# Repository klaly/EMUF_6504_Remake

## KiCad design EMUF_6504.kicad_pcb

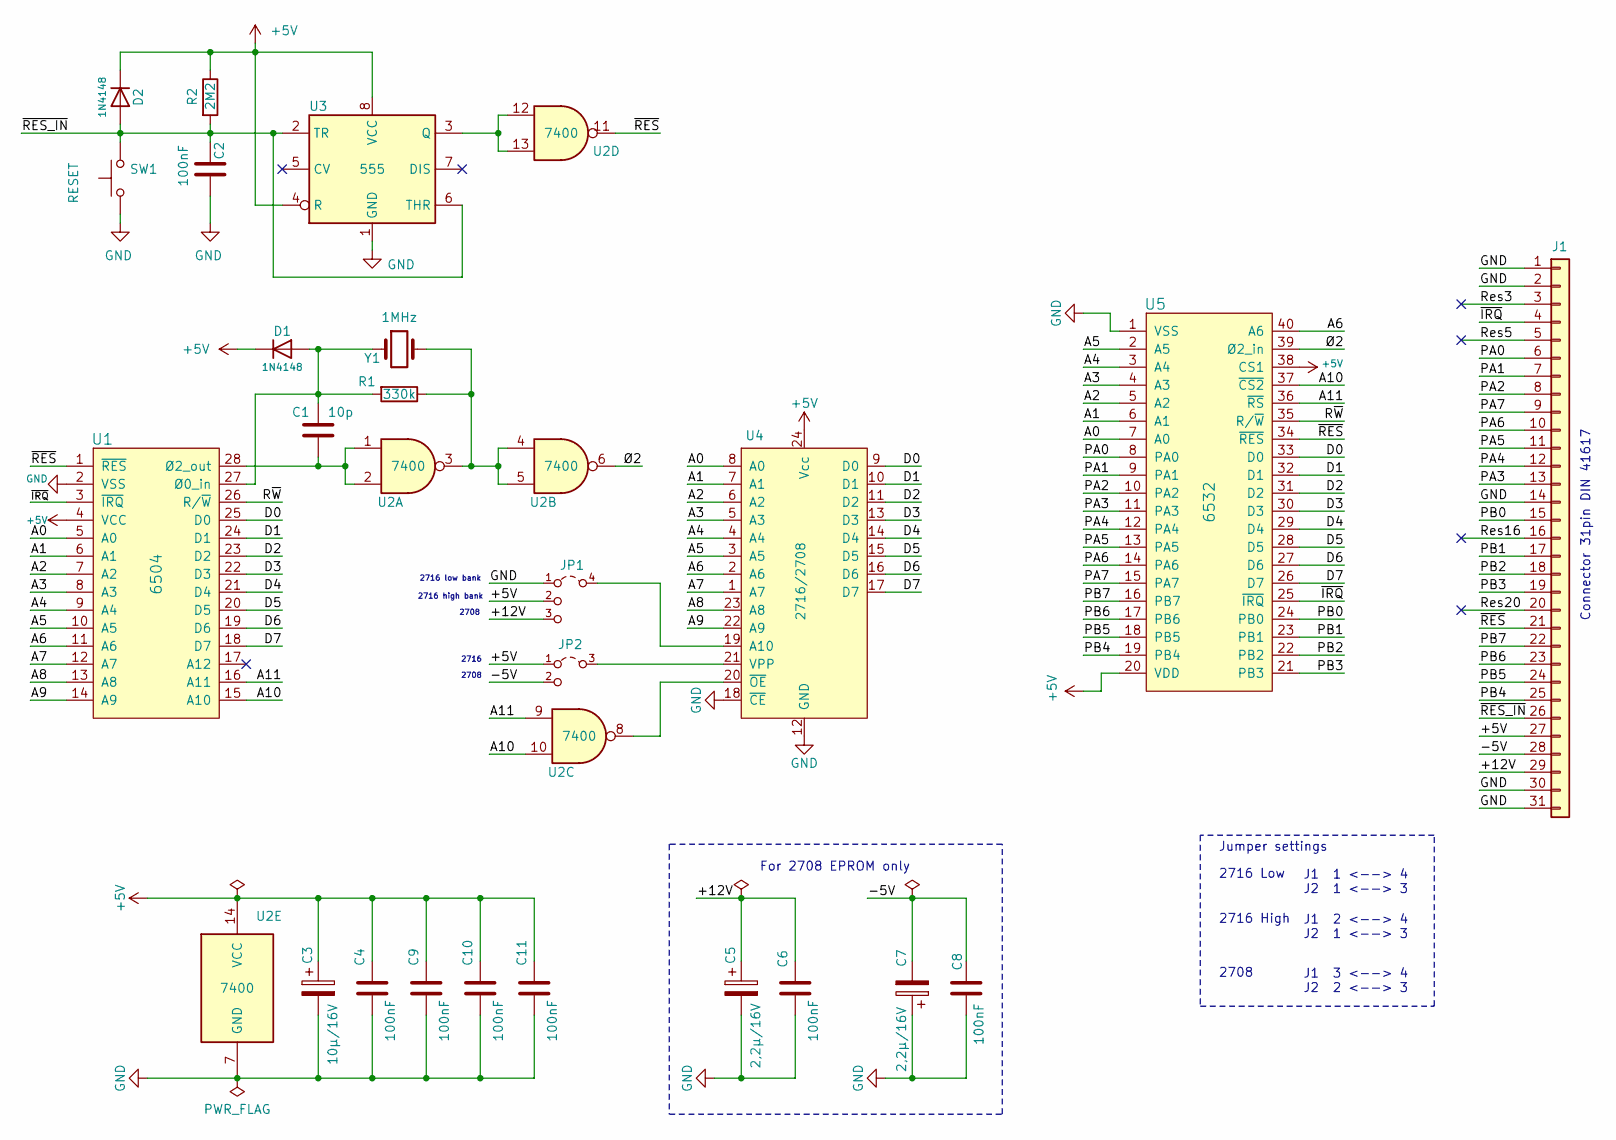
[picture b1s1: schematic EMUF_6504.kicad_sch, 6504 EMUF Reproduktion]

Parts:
C1: 10p; C_Disc_D3.8mm_W2.6mm_P2.50mm
C2: 100nF; C_Disc_D3.8mm_W2.6mm_P2.50mm
C3: 10µ/16V; CP_Radial_D5.0mm_P2.00mm
C4, C6, C8, C9, C10, C11: 100nF; C_Disc_D5.0mm_W2.5mm_P2.50mm
C5, C7: 2,2µ/16V; CP_Radial_D5.0mm_P2.00mm
D1, D2: 1N4148; D_DO-35_SOD27_P7.62mm_Horizontal
J1: Conn_01x31; Con_31_DIN41617_Stiftleiste
JP1: JUMPER4_; Jumper_4
JP2: JUMPER3_; Jumper_3
R1: 330k; R_Axial_DIN0207_L6.3mm_D2.5mm_P7.62mm_Horizontal
R2: 2M2; R_Axial_DIN0207_L6.3mm_D2.5mm_P7.62mm_Horizontal
SW1: RESET; SW_PUSH_6mm
U1: 6504; DIP-28_W15.24mm
U2: 7400; DIP-14_W7.62mm
U3: 555; DIP-8_W7.62mm
U4: 2716/2708; DIP-24_W15.24mm_Socket
U5: 6532; DIP-40_W15.24mm_Socket
Y1: 1MHz; Crystal_HC33-U_Vertical

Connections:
+5V: C3.1, C4.1, C9.1, C10.1, C11.1, D1.1 (K), D2.1 (K), J1.27, JP1.2, JP2.1, R2.1, U1.4 (VCC), U2.14 (VCC), U3.4 (R), U3.8 (VCC), U4.24 (Vcc), U5.20 (VDD), U5.38 (CS1)
/+12V: C5.1, C6.1, J1.29, JP1.3
/-5V: C7.2, C8.2, J1.28, JP2.2
/A0: U1.5 (A0), U4.8 (A0), U5.7 (A0)
/A1: U1.6 (A1), U4.7 (A1), U5.6 (A1)
/A2: U1.7 (A2), U4.6 (A2), U5.5 (A2)
/A3: U1.8 (A3), U4.5 (A3), U5.4 (A3)
/A4: U1.9 (A4), U4.4 (A4), U5.3 (A4)
/A5: U1.10 (A5), U4.3 (A5), U5.2 (A5)
/A6: U1.11 (A6), U4.2 (A6), U5.40 (A6)
/A7: U1.12 (A7), U4.1 (A7)
/A8: U1.13 (A8), U4.23 (A8)
/A9: U1.14 (A9), U4.22 (A9)
/A10: U1.15 (A10), U2.10, U5.37 (~CS2)
/A11: U1.16 (A11), U2.9, U5.36 (~RS)
/D0: U1.25 (D0), U4.9 (D0), U5.33 (D0)
/D1: U1.24 (D1), U4.10 (D1), U5.32 (D1)
/D2: U1.23 (D2), U4.11 (D2), U5.31 (D2)
/D3: U1.22 (D3), U4.13 (D3), U5.30 (D3)
/D4: U1.21 (D4), U4.14 (D4), U5.29 (D4)
/D5: U1.20 (D5), U4.15 (D5), U5.28 (D5)
/D6: U1.19 (D6), U4.16 (D6), U5.27 (D6)
/D7: U1.18 (D7), U4.17 (D7), U5.26 (D7)
/PA0: J1.6, U5.8 (PA0)
/PA1: J1.7, U5.9 (PA1)
/PA2: J1.8, U5.10 (PA2)
/PA3: J1.13, U5.11 (PA3)
/PA4: J1.12, U5.12 (PA4)
/PA5: J1.11, U5.13 (PA5)
/PA6: J1.10, U5.14 (PA6)
/PA7: J1.9, U5.15 (PA7)
/PB0: J1.15, U5.24 (PB0)
/PB1: J1.17, U5.23 (PB1)
/PB2: J1.18, U5.22 (PB2)
/PB3: J1.19, U5.21 (PB3)
/PB4: J1.25, U5.19 (PB4)
/PB5: J1.24, U5.18 (PB5)
/PB6: J1.23, U5.17 (PB6)
/PB7: J1.22, U5.16 (PB7)
/Res3: J1.3
/Res5: J1.5
/Res16: J1.16
/Res20: J1.20
/R~W: U1.26 (R/~W), U5.35 (R/~W)
/~IRQ: J1.4, U1.3 (~IRQ), U5.25 (~IRQ)
/~RES_IN: C2.1, D2.2 (A), J1.26, R2.2, SW1.2, U3.2 (TR), U3.6 (THR)
/~RES: J1.21, U1.1 (~RES), U2.11, U5.34 (~RES)
/Ø2: U2.6, U5.39 (Ø2_in)
GND: C2.2, C3.2, C4.2, C5.2, C6.2, C7.1, C8.1, C9.2, C10.2, C11.2, J1.1, J1.2, J1.14, J1.30, J1.31, JP1.1, SW1.1, U1.2 (VSS), U2.7 (GND), U3.1 (GND), U4.12 (GND), U4.18 (~CE), U5.1 (VSS)
unnamed: C1.1, D1.2 (A), R1.2, U1.27 (Ø0_in), Y1.1
unnamed: R1.1, U2.3, U2.4, U2.5, Y1.2
unnamed: C1.2, U1.28 (Ø2_out), U2.1, U2.2
unnamed: U2.12, U2.13, U3.3 (Q)
unnamed: JP1.4, U4.19 (A10)
unnamed: JP2.3, U4.21 (VPP)
unnamed: U2.8, U4.20 (~OE)

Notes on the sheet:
J1 3 <--> 4 J2 2 <--> 3
2708
J1 1 <--> 4 J2 1 <--> 3
For 2708 EPROM only
2716 High
2716
2716 high bank
Connector 31pin DIN 41617
Jumper settings
J1 2 <--> 4 J2 1 <--> 3
2716 Low
2716 low bank

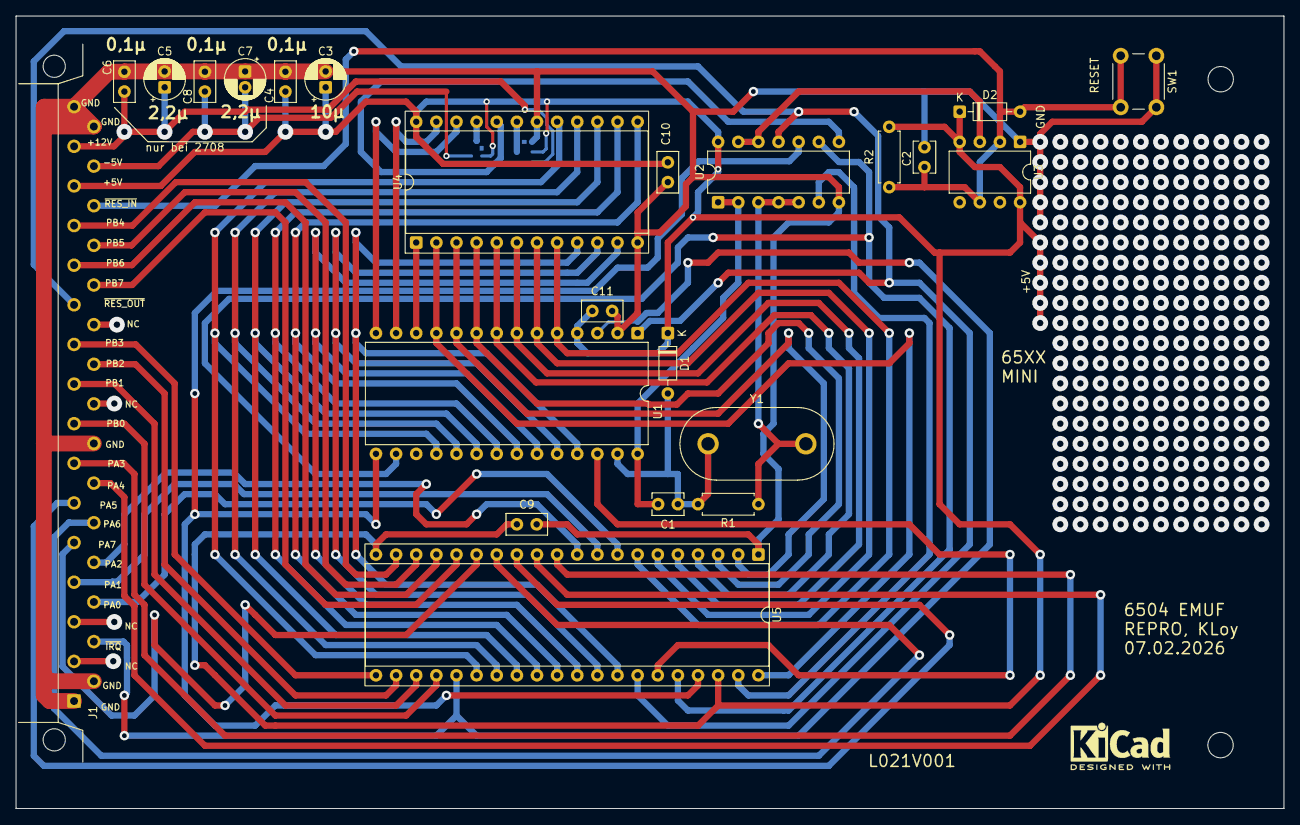
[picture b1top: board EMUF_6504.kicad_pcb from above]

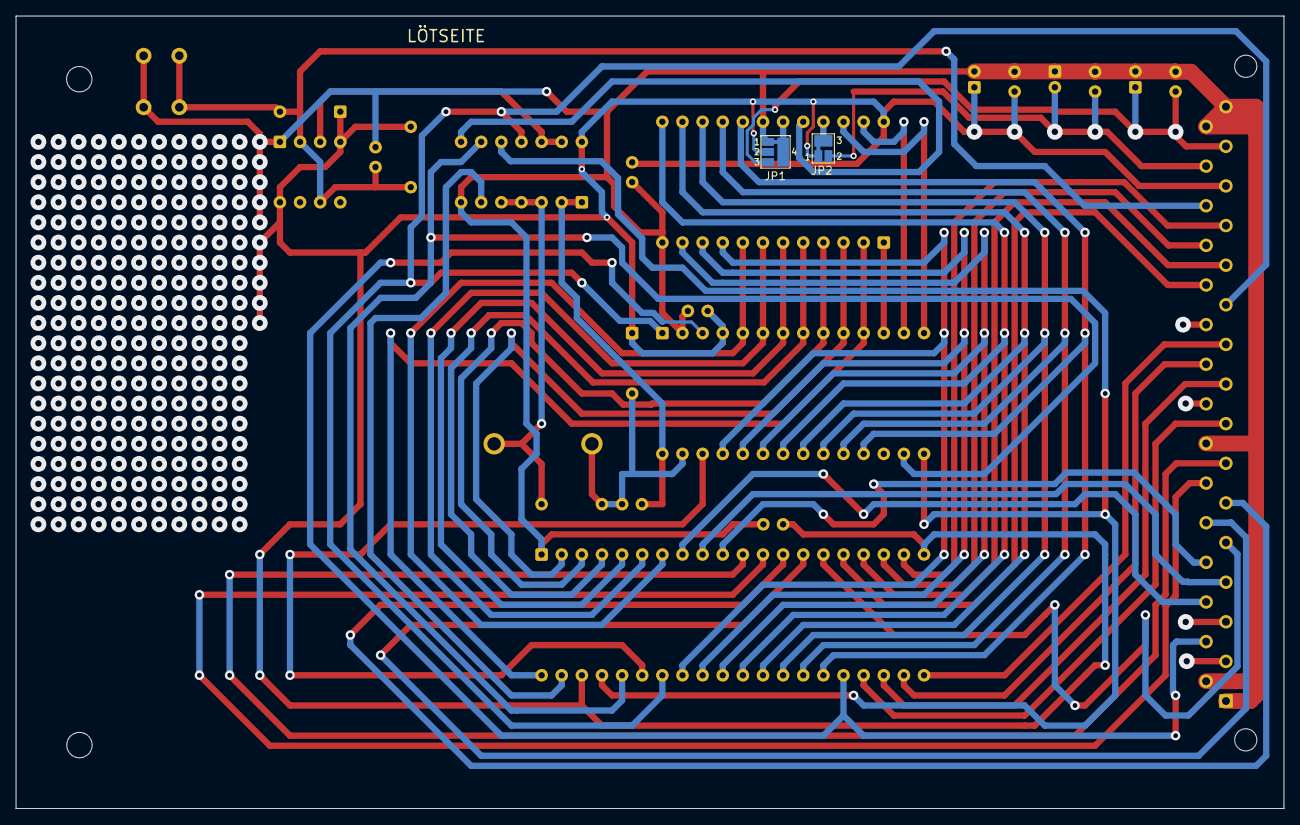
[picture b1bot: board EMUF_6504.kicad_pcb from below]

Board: 2 copper layers, 160.0 x 100.0 mm, 25 parts (2 on the bottom side), 52 nets.

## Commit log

2026-02-19 Add files via upload
    initial file upload
